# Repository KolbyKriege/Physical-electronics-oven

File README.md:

# Physical-electronics-oven
This is my Capstone project. I am making a oven for my Physical Electonic professor.

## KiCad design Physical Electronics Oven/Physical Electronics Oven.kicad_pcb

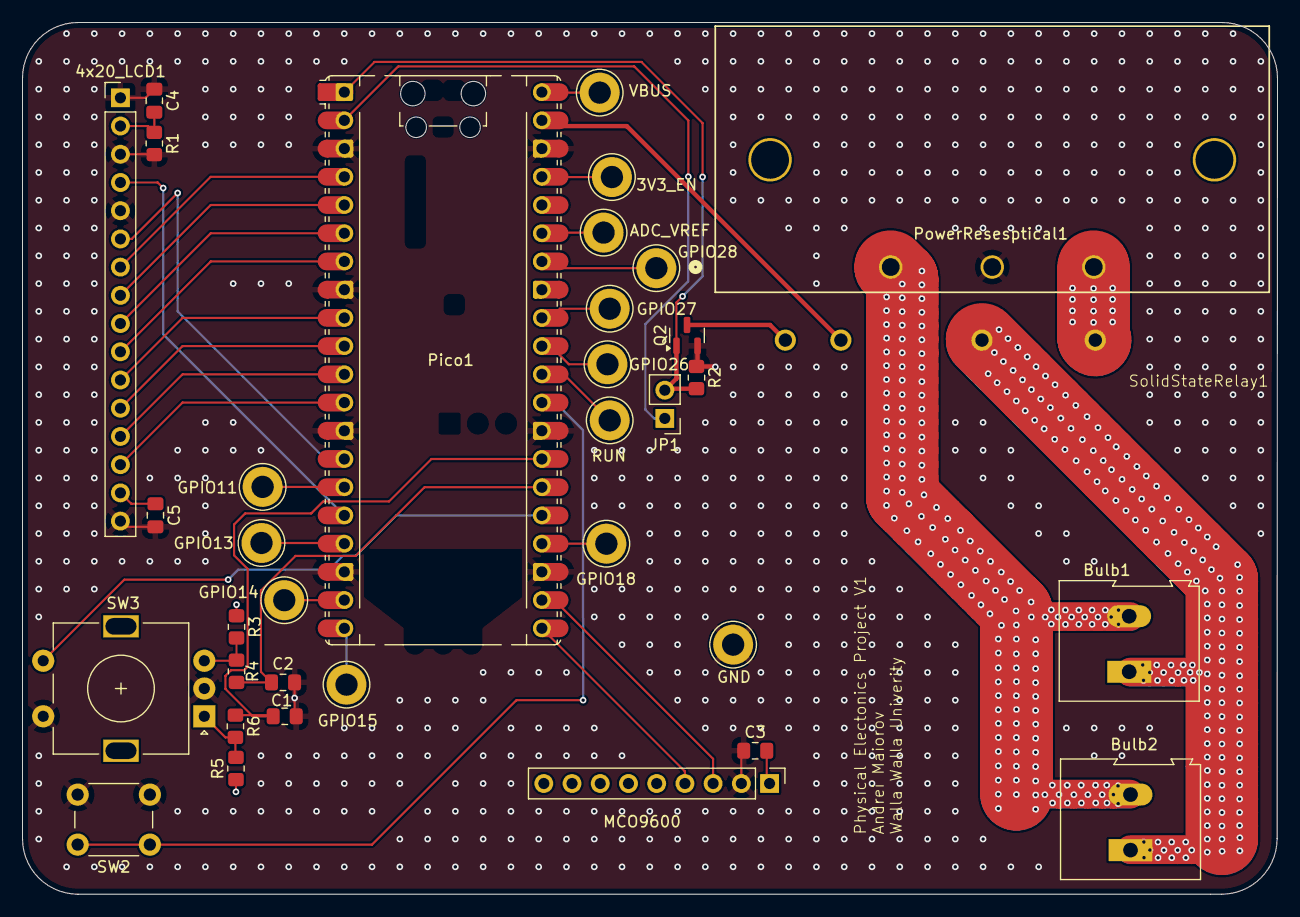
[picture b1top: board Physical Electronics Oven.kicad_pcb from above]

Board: 4 copper layers, 113.0 x 78.5 mm, 35 parts (0 on the bottom side), 39 nets.

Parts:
3V3_EN: TestPoint; TestPoint_Loop_D3.80mm_Drill2.0mm
4x20_LCD1: 4x20_LCD; PinHeader_1x16_P2.54mm_Vertical
ADC_VREF: TestPoint; TestPoint_Loop_D3.80mm_Drill2.0mm
Bulb1, Bulb2: Screw_Terminal_01x02; TerminalBlock_Altech_AK300-2_P5.00mm
C1, C2: 0.01uf; C_0805_2012Metric_Pad1.18x1.45mm_HandSolder
C3, C4, C5: 0.1uF; C_0805_2012Metric_Pad1.18x1.45mm_HandSolder
GND: TestPoint; TestPoint_Loop_D3.80mm_Drill2.0mm
GPIO11, GPIO13, GPIO14, GPIO15, GPIO18, GPIO26, GPIO27, GPIO28: TestPoint; TestPoint_Loop_D3.80mm_Drill2.0mm
JP1: Back up GIPO pin; PinHeader_1x02_P2.54mm_Vertical
MCO9600: MCP9600; PinHeader_1x09_P2.54mm_Vertical
Pico1: Pico2; RaspberryPi_Pico_Common_Unspecified
PowerResesptical1: IEC_60320_C14_Receptacle; CONN3_6ESRM-P_TEC
Q2: AO3400A; SOT-23
R1, R2, R3, R4, R5, R6: 10K; R_0805_2012Metric_Pad1.20x1.40mm_HandSolder
RUN: TestPoint; TestPoint_Loop_D3.80mm_Drill2.0mm
SW2: SW_Push; SW_PUSH_6mm
SW3: RotaryEncoder_Switch; RotaryEncoder_Alps_EC11E-Switch_Vertical_H20mm
SolidStateRelay1: SSR (PF240D25R); PF240D25R
VBUS: TestPoint; TestPoint_Loop_D3.80mm_Drill2.0mm

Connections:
3V3_EN: 3V3_EN.1, Pico1.37 (3V3_EN)
+3.3V: 4x20_LCD1.2 (Vdd), 4x20_LCD1.15 (LED+), C3.2, C4.2, C5.1, MCO9600.1 (V_in), Pico1.36 (3V3(OUT)), R1.1, R3.1, R5.1
+5V: Pico1.39 (VSYS), SolidStateRelay1.3 (DC+)
ADC_VREF: ADC_VREF.1, Pico1.35 (ADC_VREF)
GND: 4x20_LCD1.1 (Vss), 4x20_LCD1.3 (V0), 4x20_LCD1.5 (R/W), 4x20_LCD1.16 (LED-), C1.2, C2.2, C3.1, C4.1, C5.2, GND.1, MCO9600.2 (Ground), Pico1.3 (GND), Pico1.8 (GND), Pico1.13 (GND), Pico1.18 (GND), Pico1.23 (GND), Pico1.28 (GND), Pico1.38 (GND), PowerResesptical1.3 (PE), Q2.2 (S), R1.2, R2.1, SW2.2, SW3.C, SW3.S2
GPIO2: 4x20_LCD1.7 (DB0), Pico1.4 (GPIO2)
GPIO3: 4x20_LCD1.8 (DB1), Pico1.5 (GPIO3)
GPIO4: 4x20_LCD1.9 (BD2), Pico1.6 (GPIO4)
GPIO5: 4x20_LCD1.10 (DB3), Pico1.7 (GPIO5)
GPIO6: 4x20_LCD1.11 (DB4), Pico1.9 (GPIO6)
GPIO7: 4x20_LCD1.12 (DB5), Pico1.10 (GPIO7)
GPIO8: 4x20_LCD1.13 (DB6), Pico1.11 (GPIO8)
GPIO9: 4x20_LCD1.14 (DB7), Pico1.12 (GPIO9)
GPIO10: 4x20_LCD1.6 (E), Pico1.14 (GPIO10)
GPIO11: GPIO11.1, Pico1.15 (GPIO11)
GPIO12: 4x20_LCD1.4 (RS), Pico1.16 (GPIO12)
GPIO13: GPIO13.1, Pico1.17 (GPIO13)
GPIO14: GPIO14.1, Pico1.19 (GPIO14)
GPIO15: GPIO15.1, Pico1.20 (GPIO15)
GPIO18: GPIO18.1, Pico1.24 (GPIO18)
GPIO26: GPIO26.1, Pico1.31 (GPIO26)
GPIO27: GPIO27.1, Pico1.32 (GPIO27)
GPIO28: GPIO28.1, Pico1.34 (GPIO28)
unnamed: Bulb1.1, Bulb2.1, SolidStateRelay1.2 (AC_out)
unnamed: Bulb1.2, Bulb2.2, PowerResesptical1.1 (L)
unnamed: JP1.1 (A), Pico1.2 (GPIO1)
unnamed: JP1.2 (B), Pico1.1 (GPIO0), Q2.1 (G), R2.2
unnamed: MCO9600.3 (I2C_CLK), Pico1.22 (GPIO17)
unnamed: MCO9600.4 (I2C_Data), Pico1.21 (GPIO16)
unnamed: Pico1.25 (GPIO19), SW3.S1
unnamed: C2.1, Pico1.26 (GPIO20), R4.1
unnamed: C1.1, Pico1.27 (GPIO21), R6.1
unnamed: Pico1.29 (GPIO22), SW2.1
unnamed: PowerResesptical1.2 (N), SolidStateRelay1.1 (AC_in)
unnamed: Q2.3 (D), SolidStateRelay1.4 (DC-)
unnamed: R3.2, R4.2, SW3.B
unnamed: R5.2, R6.2, SW3.A
RUN: Pico1.30 (RUN), RUN.1
VBUS: Pico1.40 (VBUS), VBUS.1

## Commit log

2026-05-27 Bluk upload so C++ project fork can start
2026-05-27 removed old files
2026-05-27 added C++ readME
2026-06-02 C++ code
